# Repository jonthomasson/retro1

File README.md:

# retro1
A 6502 computer inspired by the Apple 1.

After completing the Nand2Tetris course, I had a hankering for creating an actual working computer that I could solder together and program. I took on this challenge mostly for the learning experience. My goals were to get some more experience with digital logic, learn assembly programming, and gain more familiarity with Kicad. I chose the 6502 processor since it was really well documented, fairly simple in design, and had a slew of projects I could glean information off of. These projects included The 6502 Home Computer found at grappendorf.net. This project, built by Dirk Grappendorf, was truly amazing. The level of detail he went to for the build logs and the design of the case and other areas of the computer were just incredible. This project greatly aided me in setting up the SID chip, and interfacing it with the 65C02. Another great project that helped me in getting my address decoding circuits up and running was Grant Searle's Simple 6502 Computer. Grant is a legend in my eyes. He seems to be a master at both hardware and software design. Along the path of learning, I also built an L-Star, designed by a true genius, Jac Goudsmit. Jac had the clever idea to interface the 6502 cpu with a Parallax Propeller microcontroller. The Propeller would take care of the address decoding, memory, and i/o. The L-Star works phenomenally well, and I had a blast just playing around with the Woz monitor and Apple 1 BASIC. It was the L-Star project that gave me the idea of using the Propeller to connect to the 65C02 by way of the ACIA UART. From there the Propeller outputs text onto a VGA monitor. The PS/2 Keyboard and the SD Card also interface with the Propeller chip. If you're interested in looking at some of my build/learning log, I attached it as a pdf to this project. Last but not least, the entire 6502.org forum provided a wealth of knowledge and many useful links in getting started with designing a 6502 computer.

Although this was my first computer design, I had a few design rules that I wanted to try and stick to. The first rule was that for the sake of diy, simplicity, and nostalgia for 8 bit computers of the 80s, I wanted to use mostly all through hole components. This led to a larger board size, but it would help make the finished board easier to test and modify later. I also stuck with a green solder mask, and red power led to complete the nostalgic motif. My second goal was to try and create a flexible design, that wasn't just a computer, but could also work as a learning platform later on. For this reason I tried to break out most of the unused i/o pins to edge connectors or headers that could be accessed if the need arose. Keeping with this second rule/goal, I also wanted to have a modular address decoding circuit, that I could modify and play around with. The address decoding part of the computer really fascinates me for some reason. This seems to be where a lot of the magic happens where the processor, the memory, and the i/o lines shake hands. If I found a better address scheme later on down the road, I wanted to be able to incorporate it. I finally decided on making the address module footprint the same size as a 40 pin .6" width DIP package. This way I could possibly use the Simple CPLD module I had created to act as a dynamic address decoder, or build/test any number of other schemes without needing to respin multiple boards. I've created 2 other decoding modules thus far, one giving 16K ROM, 32K RAM, and another with 32K ROM and 32K RAM (minus 256 bytes). Those modules can be found here. A third goal was to use as much of the original C64 SID circuit as possible in my design. To do this I dove into the original C64 schematics and tried to stay true to the original design as much as possible, complete with styrene filter caps.

For software I developed test scripts as I went to aid in the testing of new components. I guess this approach is similar to test driven development. This made it somewhat easy to see if modifying a circuit broke any piece of tested functionality. The finished rom has the Apple II monitor, Micro Chess, a SID synth program (taken from the Dirk Grappendorf project), a program for setting the rtc circuitry with the date/time as well as invoke the square wave output of the rtc, and a buggy version of Apple II BASIC. I say buggy version of BASIC because it's only able to run simple commands like PRINT without throwing errors. I've attempted to follow the error down the stack, but I wasn't able to figure out what I was doing wrong.

Overall I think I met my initial goals for this project. I learned a ton and had a lot of fun with it. It whet my appetite for future projects. I'm by no means an expert now, having completed the build, but I at least feel more comfortable with digital logic and computer architecture than I was before embarking on this adventure. I hope that someone may find this journey useful.
![enter image description here](https://lh3.googleusercontent.com/fglWtAJCevHwNHitfqwmh59DB7SCrmaY4Cde7DSnNZGUuWjSP1T_K4Sza81S8SkwDSR8f0cAsCZcXrHBxVfq7lEVa40fMF0jiuMtJqIvsIB2mTvOLm1gEZugCN2shx14FbcY2ICCn9GYni_Hr3OoCRJ3NOJNTxIuLEaRnTQdclNc5-4JmCeOSQDs5hj3_pFUKfmkMMD3RZiOb4AY4mAprEhdzLCM-OcGjCZ7LJ_U_UnW8B_6idliqK8M6GhG17WzaAKzX5WCYocFs9tQVj3prhMANBtD1q44_VC0PiqtTZwKPRHGvf3pS4i0vqBa5gGyxCSleta0akQDUbZ26vVzgN29EoRZqXbwIowJuD4dpYhbpNwrGQKOvZG10akbij0dUr_k_47sVvovlghGmz1eDEvNSYMJ7_vnUanjaknb8TAluUBUwwbXXYEOKqsA5p-iqbBp2RSjtZfItw-o61QujH6Z5fookMK4FzQu3joGYjcQgik6-g3tV017gighvtXwkUjbqdavWAG44vPoDuq7uQf8YDcWi8nXSl8oulNP1lsnQUAVJCpLr327_fhAIpzRiy3U48-azrM80l-8SI9SRaN4skLesd__WpcA2H90=w1688-h949-no)
![enter image description here](https://lh3.googleusercontent.com/QYqx29z2ymyEWxP5m5uKgNd9Pa6mb7tNoMsc7oYq2Ut0TmxsU7dmUhDBmqKuHvHBYXxI9zO1PFYy1nu2mCsevmKC3gORMFsfGXysLRs9zVNUyr0s0FJnZi4j0Udug8q6yaQrdhmXk3QJ9_tqXPRxoHP9WNgtqpQAlMe_dBgFVIfwTGDDCeTwBzzgiwrvfR88nAdLAQ4-y25hKn4TfD8rXsVq1a2xxI0Id7E4VsfZQ3tN5YmXVZiNZAvSt6PLiYckGK7UFSMGdzr-E_di0D0Uo7xzA6c2TorTx3M2vlX1RpKPV2DsBcJGprVH6lnGokstKRa5GP217JrhYurn79hEbUm9x18iPsnyDxzInUW21zWw9u0ExczKfQzWu_1LAH4bpiB6Vxduij-LyXyE4O9N-msowIa_P7IDBZjAU76E53f0r80ieQ6I1trgZ9EtsZyzM0ppxwFWNtqGGn_WT3clt0u6kuVGezsbDYdQdiSQTUHa-oSL8hdTwatpJyNoCosWKh2sbOtvYXGuNMh-RQZxDYHLHnvrbYrYajidoalFqE6OQQTAaI8-LGlqrowyx-N-mcE_WUjxVjkkSlrhV25zEWCaVsaOF8PETNkrOGIB=w1688-h949-no)

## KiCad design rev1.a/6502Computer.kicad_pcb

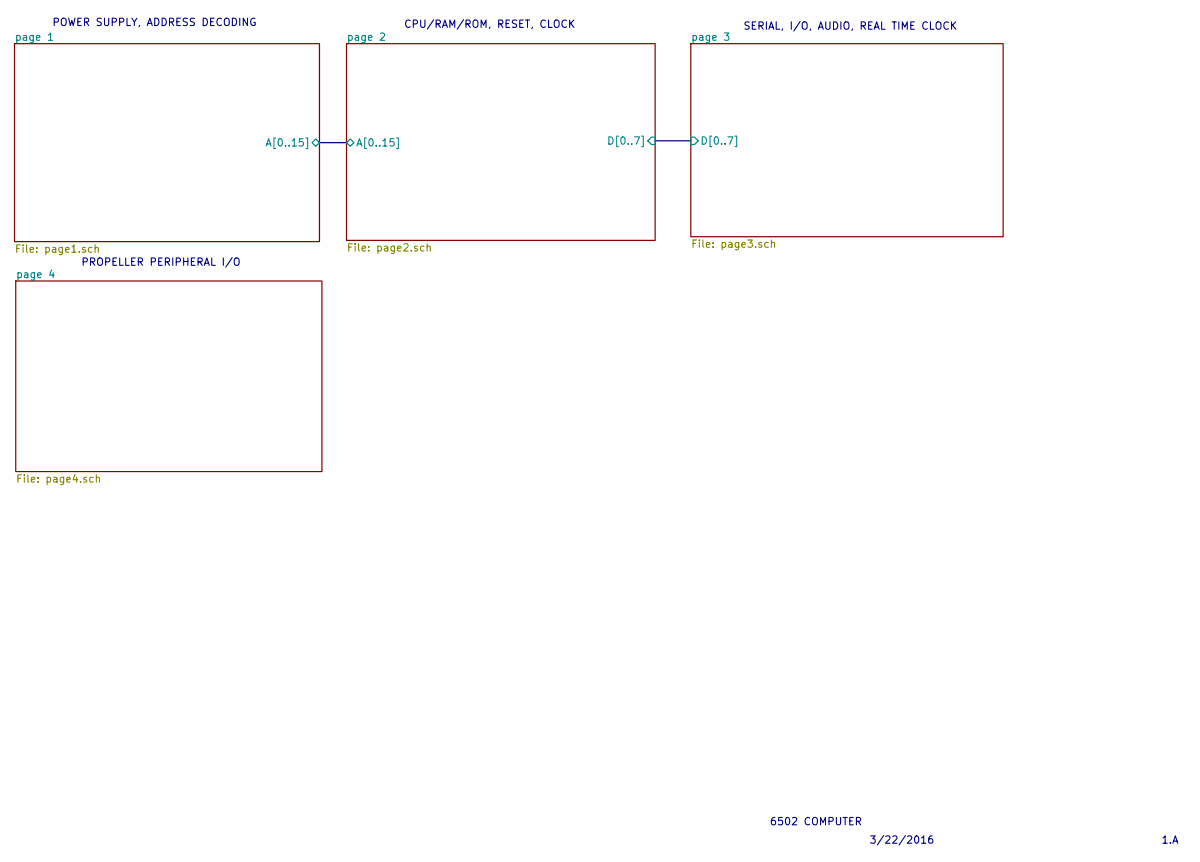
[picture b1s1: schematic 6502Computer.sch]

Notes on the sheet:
6502 COMPUTER
3/22/2016
1.A
POWER SUPPLY, ADDRESS DECODING
CPU/RAM/ROM, RESET, CLOCK
SERIAL, I/O, AUDIO, REAL TIME CLOCK
PROPELLER PERIPHERAL I/O

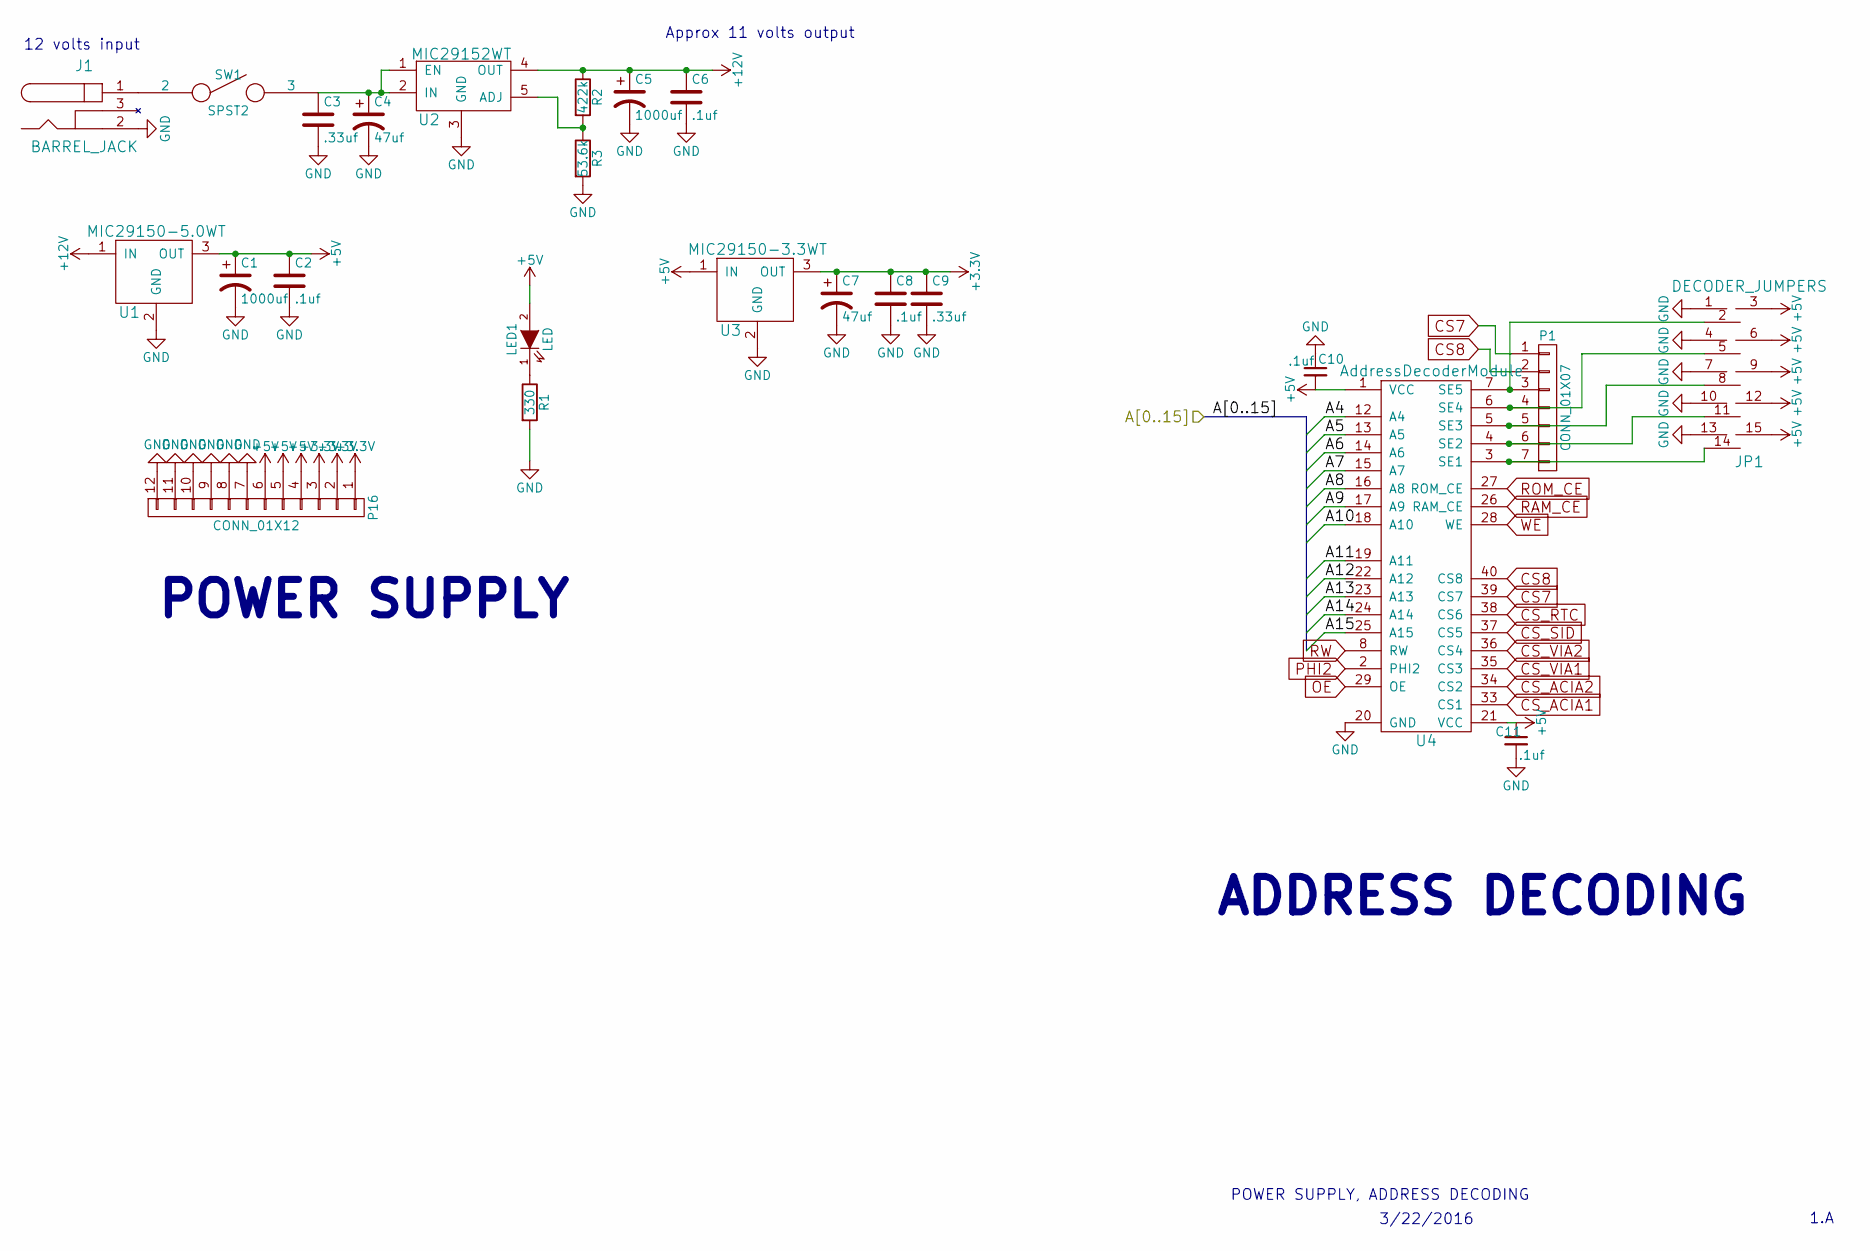
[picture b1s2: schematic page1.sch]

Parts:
C1: 1000uf; C_Radial_D10_L16_P5
C2, C6, C8, C10, C11: .1uf; C_Disc_D3_P2.5
C3, C9: .33uf; C_Disc_D6_P5
C4, C7: 47uf; C_Radial_D5_L11_P2
C5: 1000uf; C_Radial_D12.5_L25_P5
J1: BARREL_JACK; Barrel_Jack_PJ002A
JP1: DECODER_JUMPERS; Pin_Header_Straight_3x05
LED1: LED; WP1503CB_LED
P1: CONN_01X07; Socket_Strip_Straight_1x07
P16: CONN_01X12; Socket_Strip_Straight_1x12
R1: 330; Resistor_Horizontal_RM10mm
R2: 422k; Resistor_Horizontal_RM10mm
R3: 53.6k; Resistor_Horizontal_RM10mm
SW1: SPST2; SW_Micro_Right_Angle_SPST
U1: MIC29150-5.0WT; to220-horiz_5772
U2: MIC29152WT; to220-5-horiz-notab
U3: MIC29150-3.3WT; to220-horiz-notab
U4: AddressDecoderModule; Address_Decoder_CPLD2

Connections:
+3V3: C7.1, C8.1, C9.1, P16.1, P16.2, P16.3, U3.3 (OUT); also elsewhere on the board
+5V: C1.1, C2.1, C10.2, C11.1, JP1.3, JP1.6, JP1.9, JP1.12, JP1.15, LED1.2 (A), P16.4, P16.5, P16.6, U1.3 (OUT), U3.1 (IN), U4.1 (VCC), U4.21 (VCC); also elsewhere on the board
+12V: C5.1, C6.1, R2.1, U1.1 (IN), U2.4 (OUT); also elsewhere on the board
/page 1/A5: U4.13 (A5); also elsewhere on the board
/page 1/A6: U4.14 (A6); also elsewhere on the board
/page 1/A7: U4.15 (A7); also elsewhere on the board
/page 1/A8: U4.16 (A8); also elsewhere on the board
/page 1/A9: U4.17 (A9); also elsewhere on the board
/page 1/A10: U4.18 (A10); also elsewhere on the board
/page 1/A11: U4.19 (A11); also elsewhere on the board
/page 1/A12: U4.22 (A12); also elsewhere on the board
/page 1/A13: U4.23 (A13); also elsewhere on the board
/page 1/A14: U4.24 (A14); also elsewhere on the board
/page 1/A15: U4.25 (A15); also elsewhere on the board
A4: U4.12 (A4); also elsewhere on the board
CS7: P1.1, U4.39 (CS7)
CS8: P1.2, U4.40 (CS8)
CS_ACIA1: U4.33 (CS1); also elsewhere on the board
CS_ACIA2: U4.34 (CS2); also elsewhere on the board
CS_RTC: U4.38 (CS6); also elsewhere on the board
CS_SID: U4.37 (CS5); also elsewhere on the board
CS_VIA1: U4.35 (CS3); also elsewhere on the board
CS_VIA2: U4.36 (CS4); also elsewhere on the board
GND: C1.2, C2.2, C3.2, C4.2, C5.2, C6.2, C7.2, C8.2, C9.2, C10.1, C11.2, J1.2, JP1.1, JP1.4, JP1.7, JP1.10, JP1.13, P16.7, P16.8, P16.9, P16.10, P16.11, P16.12, R1.2, R3.2, U1.2 (GND), U2.3 (GND), U3.2 (GND), U4.20 (GND); also elsewhere on the board
unnamed: C3.1, C4.1, SW1.3, U2.1 (EN), U2.2 (IN)
unnamed: J1.1, SW1.2
unnamed: JP1.2, P1.3, U4.7 (SE5)
unnamed: JP1.5, P1.4, U4.6 (SE4)
unnamed: JP1.8, P1.5, U4.5 (SE3)
unnamed: JP1.11, P1.6, U4.4 (SE2)
unnamed: JP1.14, P1.7, U4.3 (SE1)
unnamed 105: LED1.1 (K), R1.1; also elsewhere on the board
unnamed: R2.2, R3.1, U2.5 (ADJ)
OE: U4.29 (OE); also elsewhere on the board
PHI2: U4.2 (PHI2); also elsewhere on the board
RAM_CE: U4.26 (RAM_CE); also elsewhere on the board
ROM_CE: U4.27 (ROM_CE); also elsewhere on the board
RW: U4.8 (RW); also elsewhere on the board
WE: U4.28 (WE); also elsewhere on the board

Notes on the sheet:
ADDRESS DECODING
POWER SUPPLY
Approx 11 volts output
12 volts input
POWER SUPPLY, ADDRESS DECODING
3/22/2016
1.A

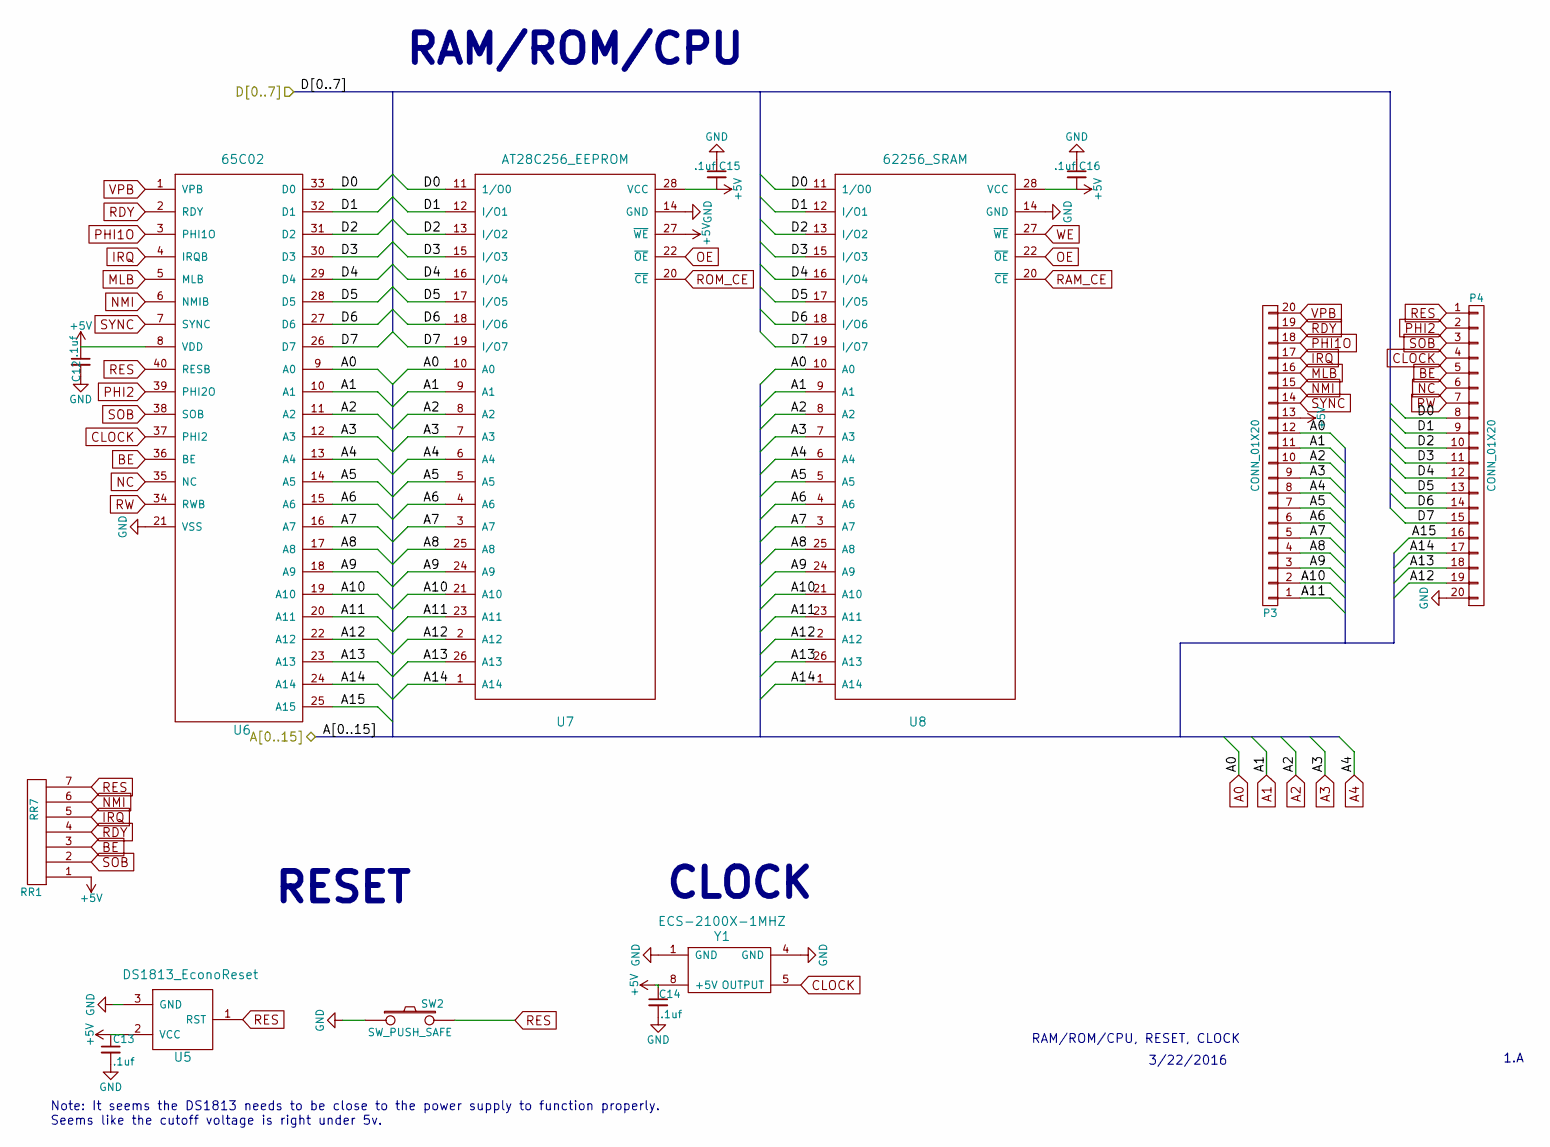
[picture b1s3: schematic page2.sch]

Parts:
C12, C13, C14, C15, C16: .1uf; C_Disc_D3_P2.5
P3, P4: CONN_01X20; Socket_Strip_Straight_1x20
RR1: RR7; 7_pin_resistor_network
SW2: SW_PUSH_SAFE; 1-1825027-1-TACTILE_SWITCH
U5: DS1813_EconoReset; TO-92_Molded_Narrow
U6: 65C02; dil_40-600_socket
U7: AT28C256_EEPROM; 28-526-11-SOCKET
U8: 62256_SRAM; dil_28-600_socket
Y1: ECS-2100X-1MHZ; ECS-2100AX

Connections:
+5V: C12.1, C13.1, C14.1, C15.2, C16.2, P3.13, RR1.1 (COM), U5.2 (VCC), U6.8 (VDD), U7.27 (~WE), U7.28 (VCC), U8.28 (VCC), Y1.8 (+5V); also elsewhere on the board
/page 1/A5: P3.7, U6.14 (A5), U7.5 (A5), U8.5 (A5); also elsewhere on the board
/page 1/A6: P3.6, U6.15 (A6), U7.4 (A6), U8.4 (A6); also elsewhere on the board
/page 1/A7: P3.5, U6.16 (A7), U7.3 (A7), U8.3 (A7); also elsewhere on the board
/page 1/A8: P3.4, U6.17 (A8), U7.25 (A8), U8.25 (A8); also elsewhere on the board
/page 1/A9: P3.3, U6.18 (A9), U7.24 (A9), U8.24 (A9); also elsewhere on the board
/page 1/A10: P3.2, U6.19 (A10), U7.21 (A10), U8.21 (A10); also elsewhere on the board
/page 1/A11: P3.1, U6.20 (A11), U7.23 (A11), U8.23 (A11); also elsewhere on the board
/page 1/A12: P4.19, U6.22 (A12), U7.2 (A12), U8.2 (A12); also elsewhere on the board
/page 1/A13: P4.18, U6.23 (A13), U7.26 (A13), U8.26 (A13); also elsewhere on the board
/page 1/A14: P4.17, U6.24 (A14), U7.1 (A14), U8.1 (A14); also elsewhere on the board
/page 1/A15: P4.16, U6.25 (A15); also elsewhere on the board
/page 2/D0: P4.8, U6.33 (D0), U7.11 (1/O0), U8.11 (1/O0); also elsewhere on the board
/page 2/D1: P4.9, U6.32 (D1), U7.12 (I/O1), U8.12 (I/O1); also elsewhere on the board
/page 2/D2: P4.10, U6.31 (D2), U7.13 (I/O2), U8.13 (I/O2); also elsewhere on the board
/page 2/D3: P4.11, U6.30 (D3), U7.15 (I/O3), U8.15 (I/O3); also elsewhere on the board
/page 2/D4: P4.12, U6.29 (D4), U7.16 (I/O4), U8.16 (I/O4); also elsewhere on the board
/page 2/D5: P4.13, U6.28 (D5), U7.17 (I/O5), U8.17 (I/O5); also elsewhere on the board
/page 2/D6: P4.14, U6.27 (D6), U7.18 (I/O6), U8.18 (I/O6); also elsewhere on the board
/page 2/D7: P4.15, U6.26 (D7), U7.19 (I/O7), U8.19 (I/O7); also elsewhere on the board
A0: P3.12, U6.9 (A0), U7.10 (A0), U8.10 (A0); also elsewhere on the board
A1: P3.11, U6.10 (A1), U7.9 (A1), U8.9 (A1); also elsewhere on the board
A2: P3.10, U6.11 (A2), U7.8 (A2), U8.8 (A2); also elsewhere on the board
A3: P3.9, U6.12 (A3), U7.7 (A3), U8.7 (A3); also elsewhere on the board
A4: P3.8, U6.13 (A4), U7.6 (A4), U8.6 (A4); also elsewhere on the board
BE: P4.5, RR1.3, U6.36 (BE)
CLOCK: P4.4, U6.37 (PHI2), Y1.5 (OUTPUT)
GND: C12.2, C13.2, C14.2, C15.1, C16.1, P4.20, SW2.1, U5.3 (GND), U6.21 (VSS), U7.14 (GND), U8.14 (GND), Y1.1 (GND), Y1.4 (GND); also elsewhere on the board
IRQ: P3.17, RR1.5, U6.4 (IRQB); also elsewhere on the board
MLB: P3.16, U6.5 (MLB)
NC: P4.6, U6.35 (NC)
NMI: P3.15, RR1.6, U6.6 (NMIB); also elsewhere on the board
OE: U7.22 (~OE), U8.22 (~OE); also elsewhere on the board
PHI1O: P3.18, U6.3 (PHI1O)
PHI2: P4.2, U6.39 (PHI2O); also elsewhere on the board
RAM_CE: U8.20 (~CE); also elsewhere on the board
RDY: P3.19, RR1.4, U6.2 (RDY)
RES: P4.1, RR1.7, SW2.4, U5.1 (RST), U6.40 (RESB); also elsewhere on the board
ROM_CE: U7.20 (~CE); also elsewhere on the board
RW: P4.7, U6.34 (RWB); also elsewhere on the board
SOB: P4.3, RR1.2, U6.38 (SOB)
SYNC: P3.14, U6.7 (SYNC)
VPB: P3.20, U6.1 (VPB)
WE: U8.27 (~WE); also elsewhere on the board

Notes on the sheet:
RAM/ROM/CPU
CLOCK
RESET
Note: It seems the DS1813 needs to be close to the power supply to function properly. Seems like the cutoff voltage is right under 5v.
RAM/ROM/CPU, RESET, CLOCK
3/22/2016
1.A

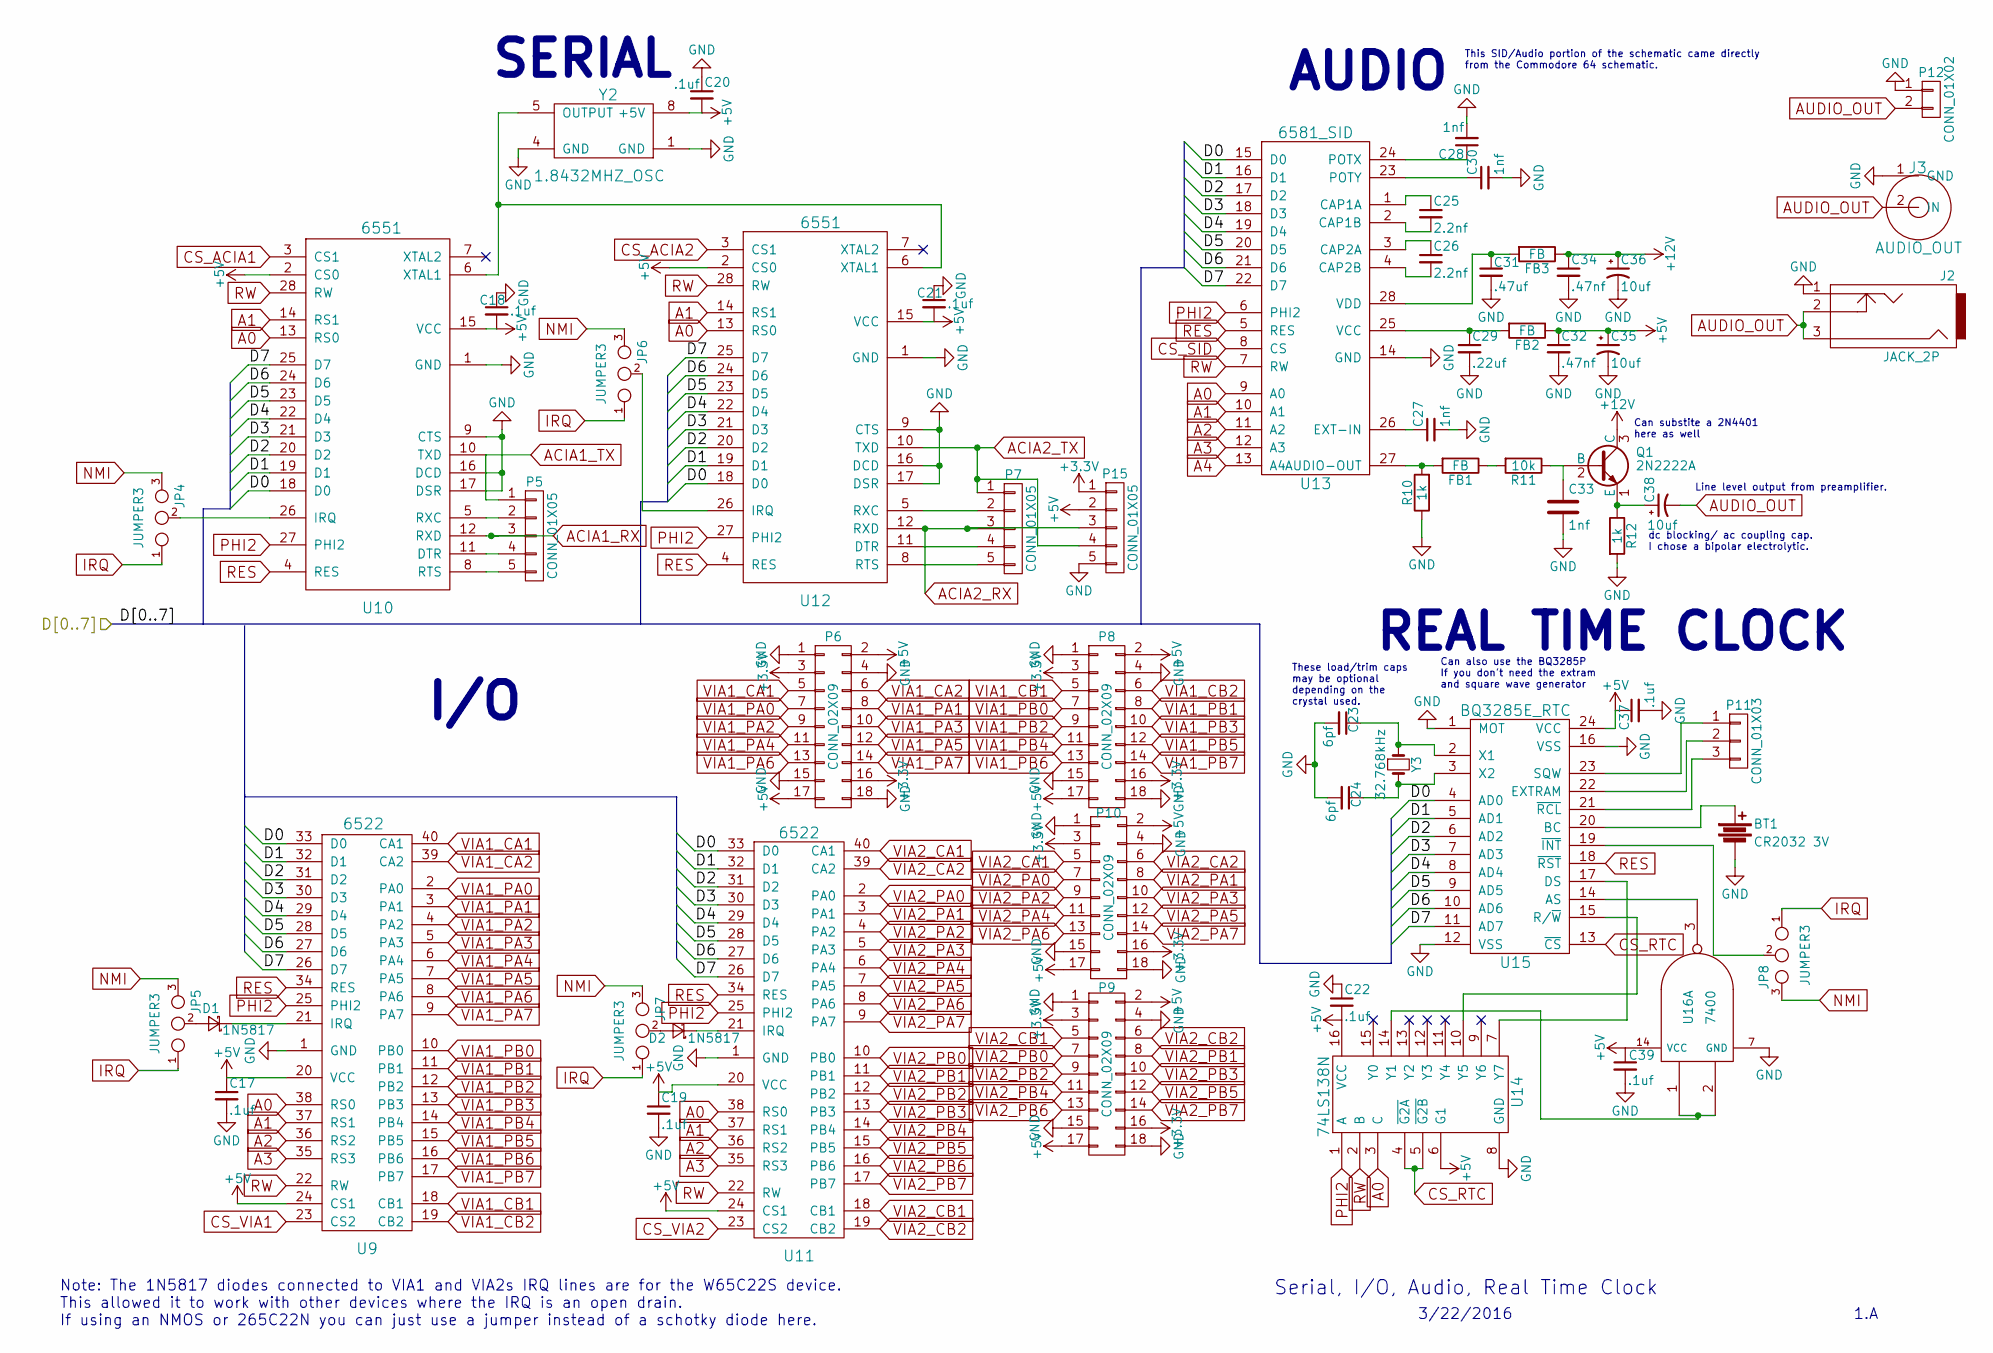
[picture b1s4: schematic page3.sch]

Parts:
BT1: CR2032 3V; BU2032SM
C17, C18, C19, C20, C21, C22, C37, C39: .1uf; C_Disc_D3_P2.5
C23, C24: 6pf; C_Disc_D3_P2.5
C25, C26: 2.2nf; C_Axial_D6_L11_P18
C27, C28, C30, C33: 1nf; C_Disc_D6_P3.5_Skinny
C29: .22uf; C_Disc_D3_P2.5
C31: .47uf; C_Disc_D3_P2.5
C32, C34: .47nf; C_Disc_D3_P2.5
C35, C36: 10uf; C_Radial_D5_L11_P2
C38: 10uf; C_Radial_D12.5_L25_P5
D1, D2: 1N5817; diode_do41
FB1, FB2, FB3: FB; Ferrite_Bead_Horizontal_RM10mm
J2: JACK_2P; SJ13525NHeadphone
J3: AUDIO_OUT; RCJ013AUDIO
JP4, JP5, JP6, JP7, JP8: JUMPER3; Pin_Header_Straight_1x03
P5, P7: CONN_01X05; Socket_Strip_Straight_1x05
P6, P8, P9, P10: CONN_02X09; Socket_Strip_Angled_2x09
P11: CONN_01X03; Socket_Strip_Straight_1x03
P12: CONN_01X02; Socket_Strip_Straight_1x02
P15: CONN_01X05; Pin_Header_Angled_1x05
Q1: 2N2222A; TO-92_Molded_Narrow
R10, R12: 1k; Resistor_Horizontal_RM10mm
R11: 10k; Resistor_Horizontal_RM10mm
U9, U11: 6522; dil_40-600_socket
U10, U12: 6551; dil_28-600_socket
U13: 6581_SID; dil_28-600_socket
U14: 74LS138N; dil_16-300_socket
U15: BQ3285E_RTC; dil_24-600_socket
U16: 7400; dil_14-300_socket
Y2: 1.8432MHZ_OSC; ECS-2100AX
Y3: 32.768kHz; crystal_tc-38_horiz

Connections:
+3V3: P6.3, P6.16, P8.3, P8.16, P9.3, P9.16, P10.3, P10.16, P15.1; also elsewhere on the board
+5V: C17.1, C18.2, C19.1, C20.2, C21.2, C22.2, C32.1, C35.1, C37.1, C39.1, FB2.1, P6.2, P6.17, P8.2, P8.17, P9.2, P9.17, P10.2, P10.17, P15.2, U9.20 (VCC), U9.24 (CS1), U10.2 (CS0), U10.15 (VCC), U11.20 (VCC), U11.24 (CS1), U12.2 (CS0), U12.15 (VCC), U14.6 (G1), U14.16 (VCC), U15.24 (VCC), U16.14 (VCC), Y2.8 (+5V); also elsewhere on the board
+12V: C34.1, C36.1, FB3.1, Q1.3 (C); also elsewhere on the board
/page 2/D0: U9.33 (D0), U10.18 (D0), U11.33 (D0), U12.18 (D0), U13.15 (D0), U15.4 (AD0); also elsewhere on the board
/page 2/D1: U9.32 (D1), U10.19 (D1), U11.32 (D1), U12.19 (D1), U13.16 (D1), U15.5 (AD1); also elsewhere on the board
/page 2/D2: U9.31 (D2), U10.20 (D2), U11.31 (D2), U12.20 (D2), U13.17 (D2), U15.6 (AD2); also elsewhere on the board
/page 2/D3: U9.30 (D3), U10.21 (D3), U11.30 (D3), U12.21 (D3), U13.18 (D3), U15.7 (AD3); also elsewhere on the board
/page 2/D4: U9.29 (D4), U10.22 (D4), U11.29 (D4), U12.22 (D4), U13.19 (D4), U15.8 (AD4); also elsewhere on the board
/page 2/D5: U9.28 (D5), U10.23 (D5), U11.28 (D5), U12.23 (D5), U13.20 (D5), U15.9 (AD5); also elsewhere on the board
/page 2/D6: U9.27 (D6), U10.24 (D6), U11.27 (D6), U12.24 (D6), U13.21 (D6), U15.10 (AD6); also elsewhere on the board
/page 2/D7: U9.26 (D7), U10.25 (D7), U11.26 (D7), U12.25 (D7), U13.22 (D7), U15.11 (AD7); also elsewhere on the board
A0: U9.38 (RS0), U10.13 (RS0), U11.38 (RS0), U12.13 (RS0), U13.9 (A0), U14.3 (C); also elsewhere on the board
A1: U9.37 (RS1), U10.14 (RS1), U11.37 (RS1), U12.14 (RS1), U13.10 (A1); also elsewhere on the board
A2: U9.36 (RS2), U11.36 (RS2), U13.11 (A2); also elsewhere on the board
A3: U9.35 (RS3), U11.35 (RS3), U13.12 (A3); also elsewhere on the board
A4: U13.13 (A4); also elsewhere on the board
ACIA1_RX: P5.3, U10.12 (RXD); also elsewhere on the board
ACIA1_TX: P5.1, U10.10 (TXD); also elsewhere on the board
ACIA2_RX: P7.3, P15.3, U12.12 (RXD); also elsewhere on the board
ACIA2_TX: P7.1, P15.4, U12.10 (TXD); also elsewhere on the board
AUDIO_OUT: C38.2, J2.2, J2.3, J3.2 (IN), P12.2
CS_RTC: U14.4 (~G2A), U14.5 (~G2B), U15.13 (~CS); also elsewhere on the board
CS_SID: U13.8 (CS); also elsewhere on the board
CS_VIA1: U9.23 (CS2); also elsewhere on the board
CS_VIA2: U11.23 (CS2); also elsewhere on the board
GND: BT1.2, C17.2, C18.1, C19.2, C20.1, C21.1, C22.1, C23.2, C24.2, C27.2, C28.2, C29.2, C30.2, C31.2, C32.2, C33.2, C34.2, C35.2, C36.2, C37.2, C39.2, J2.1, J3.1 (GND), P6.1, P6.4, P6.15, P6.18, P8.1, P8.4, P8.15, P8.18, P9.1, P9.4, P9.15, P9.18, P10.1, P10.4, P10.15, P10.18, P12.1, P15.5, R10.1, R12.2, U9.1 (GND), U10.1 (GND), U10.9 (CTS), U10.16 (DCD), U10.17 (DSR), U11.1 (GND), U12.1 (GND), U12.9 (CTS), U12.16 (DCD), U12.17 (DSR), U13.14 (GND), U14.8 (GND), U15.1 (MOT), U15.12 (VSS), U15.16 (VSS), U16.7 (GND), Y2.1 (GND), Y2.4 (GND); also elsewhere on the board
IRQ: JP4.1, JP5.1, JP6.1, JP7.1, JP8.1; also elsewhere on the board
NMI: JP4.3, JP5.3, JP6.3, JP7.3, JP8.3; also elsewhere on the board
unnamed: BT1.1, U15.20 (BC)
unnamed: C23.1, U15.2 (X1), Y3.1
unnamed: C24.1, U15.3 (X2), Y3.2
unnamed: C25.1, U13.1 (CAP1A)
unnamed: C25.2, U13.2 (CAP1B)
unnamed: C26.1, U13.3 (CAP2A)
unnamed: C26.2, U13.4 (CAP2B)
unnamed: C27.1, U13.26 (EXT-IN)
unnamed: C28.1, U13.24 (POTX)
unnamed: C29.1, FB2.2, U13.25 (VCC)
unnamed: C30.1, U13.23 (POTY)
unnamed: C31.1, FB3.2, U13.28 (VDD)
unnamed: C33.1, Q1.2 (B), R11.1
unnamed: C38.1, Q1.1 (E), R12.1
unnamed: D1.1 (K), U9.21 (IRQ)
unnamed: D1.2 (A), JP5.2
unnamed: D2.1 (K), U11.21 (IRQ)
unnamed: D2.2 (A), JP7.2
unnamed: FB1.1, R11.2
unnamed: FB1.2, R10.2, U13.27 (AUDIO-OUT)
unnamed 91: JP4.2, U10.26 (IRQ); also elsewhere on the board
unnamed 92: JP6.2, U12.26 (IRQ); also elsewhere on the board
unnamed: JP8.2, U15.19 (~INT)
unnamed 106: P5.2, U10.5 (RXC); also elsewhere on the board
unnamed 107: P5.4, U10.11 (DTR); also elsewhere on the board
unnamed 108: P5.5, U10.8 (RTS); also elsewhere on the board
unnamed 109: P7.2, U12.5 (RXC); also elsewhere on the board
unnamed 110: P7.4, U12.11 (DTR); also elsewhere on the board
unnamed 111: P7.5, U12.8 (RTS); also elsewhere on the board
unnamed: P11.1, U15.23 (SQW)
unnamed: P11.2, U15.22 (EXTRAM)
unnamed: P11.3, U15.21 (~RCL)
unnamed 137: U10.6 (XTAL1), U12.6 (XTAL1), Y2.5 (OUTPUT); also elsewhere on the board
unnamed: U14.7 (Y7), U15.17 (DS)
unnamed: U14.10 (Y5), U15.15 (R/~W)
unnamed: U14.14 (Y1), U16.1, U16.2
unnamed: U15.14 (AS), U16.3
PHI2: U9.25 (PHI2), U10.27 (PHI2), U11.25 (PHI2), U12.27 (PHI2), U13.6 (PHI2), U14.1 (A); also elsewhere on the board
RES: U9.34 (RES), U10.4 (RES), U11.34 (RES), U12.4 (RES), U13.5 (RES), U15.18 (~RST); also elsewhere on the board
RW: U9.22 (RW), U10.28 (RW), U11.22 (RW), U12.28 (RW), U13.7 (RW), U14.2 (B); also elsewhere on the board
VIA1_CA1: P6.5, U9.40 (CA1)
VIA1_CA2: P6.6, U9.39 (CA2)
VIA1_CB1: P8.5, U9.18 (CB1)
VIA1_CB2: P8.6, U9.19 (CB2)
VIA1_PA0: P6.7, U9.2 (PA0)
VIA1_PA1: P6.8, U9.3 (PA1)
VIA1_PA2: P6.9, U9.4 (PA2)
VIA1_PA3: P6.10, U9.5 (PA3)
VIA1_PA4: P6.11, U9.6 (PA4)
VIA1_PA5: P6.12, U9.7 (PA5)
VIA1_PA6: P6.13, U9.8 (PA6)
VIA1_PA7: P6.14, U9.9 (PA7)
VIA1_PB0: P8.7, U9.10 (PB0)
VIA1_PB1: P8.8, U9.11 (PB1)
VIA1_PB2: P8.9, U9.12 (PB2)
VIA1_PB3: P8.10, U9.13 (PB3)
VIA1_PB4: P8.11, U9.14 (PB4)
VIA1_PB5: P8.12, U9.15 (PB5)
VIA1_PB6: P8.13, U9.16 (PB6)
VIA1_PB7: P8.14, U9.17 (PB7)
VIA2_CA1: P10.5, U11.40 (CA1)
VIA2_CA2: P10.6, U11.39 (CA2)
VIA2_CB1: P9.5, U11.18 (CB1)
VIA2_CB2: P9.6, U11.19 (CB2)
VIA2_PA0: P10.7, U11.2 (PA0)
VIA2_PA1: P10.8, U11.3 (PA1)
VIA2_PA2: P10.9, U11.4 (PA2)
VIA2_PA3: P10.10, U11.5 (PA3)
VIA2_PA4: P10.11, U11.6 (PA4)
VIA2_PA5: P10.12, U11.7 (PA5)
VIA2_PA6: P10.13, U11.8 (PA6)
VIA2_PA7: P10.14, U11.9 (PA7)
VIA2_PB0: P9.7, U11.10 (PB0)
VIA2_PB1: P9.8, U11.11 (PB1)
VIA2_PB2: P9.9, U11.12 (PB2)
VIA2_PB3: P9.10, U11.13 (PB3)
VIA2_PB4: P9.11, U11.14 (PB4)
VIA2_PB5: P9.12, U11.15 (PB5)
VIA2_PB6: P9.13, U11.16 (PB6)
VIA2_PB7: P9.14, U11.17 (PB7)

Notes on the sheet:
AUDIO
I/O
SERIAL
REAL TIME CLOCK
Note: The 1N5817 diodes connected to VIA1 and VIA2s IRQ lines are for the W65C22S device. This allowed it to work with other devices where the IRQ is an open drain. If using an NMOS or 265C22N you can just use a jumper instead of a schotky diode here.
Can substite a 2N4401 here as well
Can also use the BQ3285P If you don't need the extram and square wave generator
This SID/Audio portion of the schematic came directly from the Commodore 64 schematic.
These load/trim caps may be optional depending on the crystal used.
Serial, I/O, Audio, Real Time Clock
3/22/2016
1.A
dc blocking/ ac coupling cap. I chose a bipolar electrolytic.
Line level output from preamplifier.
